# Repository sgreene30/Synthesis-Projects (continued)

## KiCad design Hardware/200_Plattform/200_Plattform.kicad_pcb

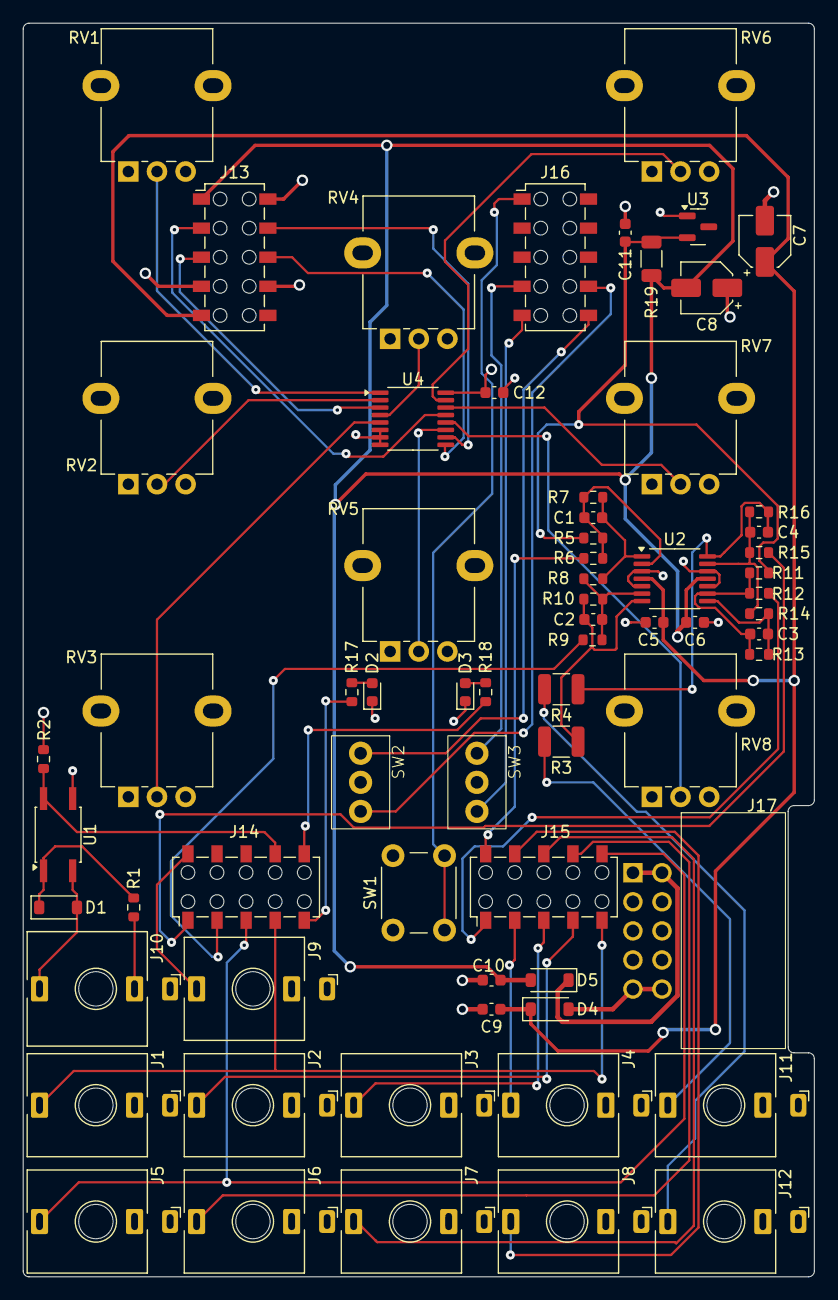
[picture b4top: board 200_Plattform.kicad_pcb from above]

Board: 4 copper layers, 69.1 x 109.5 mm, 69 parts (1 on the bottom side), 55 nets.

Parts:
C1, C2, C3, C4: 180pF; C_0603_1608Metric
C5, C6, C9, C10, C11, C12: 100nF; C_0603_1608Metric
C7, C8: 10uF; CAP_EEE-FK1V100UR
D1, D4, D5: MBR0530; D_SOD-123
D2, D3: LED_BLUE; LED_0603_1608Metric
J1, J2, J3, J4, J5, J6, J7, J8, J9, J11, J12: THONKICONN_MONO; JACK_THONKICONN_MONO_WQP518MA
J10: THONKICONN STEREO; JACK_THONKICONN_STEREO_WQP419GR
J13, J14, J15, J16: HEADER_2X10_BOTTOM_ENTRY_966210-2000-AR-PR
J17: EURO_POWER_10_RTANG
M1: DAISY PATCH SM; DAISY_PATCH_SM_OUTLINE
R1, R2, R17, R18: 220R; R_0603_1608Metric
R3, R4: 1k 0.5W; R_1210_3225Metric
R5, R7, R11, R13: 20k; R_0603_1608Metric
R6, R8, R9, R10, R12, R14, R15, R16: 10k; R_0603_1608Metric
R19: 6.8k 0.25W; R_1206_3216Metric
RV1, RV2, RV3, RV4, RV5, RV6, RV7, RV8: 10k; ALPHAPOT
SW1: SW_TACTILE; SW_TACTILE_TL1105SPF250Q
SW2, SW3: SW_SPDT_ON_OFF_ON_SUBMINI; SW_TOGGLE_2MS3T1B3M2QES
U1: LTV-355T; SO-4_4.4x3.6mm_P2.54mm
U2: TL074CPWR; TSSOP-14_4.4x5mm_P0.65mm
U3: LM4040CIM3-5.0; SOT-23
U4: CD4052B; TSSOP-16_4.4x5mm_P0.65mm

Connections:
+3.3V: C12.1, J13.10 (X10), R2.2, RV1.3, RV2.3, RV3.3, RV4.3, RV5.3, RV6.3, RV7.3, RV8.3, U4.16 (VDD)
+12V: C5.1, C7.1, C9.1, D4.1 (K), J13.5 (X5), U2.4 (V+)
-5V: C11.1, R5.1, R11.1, R19.1, U3.2 (A)
-12V: C6.2, C8.2, C10.2, D5.2 (A), J13.1 (X1), R19.2, U2.11 (V-)
/Jacks/MIDI_SINK: D1.2 (A), J10.T, U1.2
/Jacks/MIDI_SOURCE: J10.R, R1.1
AUDIO_LEFT: J14.2 (X2), R9.1
AUDIO_RIGHT: J14.1 (X1), R15.1
CV_OUT_1: J15.10 (X10), R6.2
CV_OUT_2: J15.1 (X1), R12.2
GATE_IN: J9.T, J14.10 (X10)
GND: C5.2, C6.1, C7.2, C8.1, C9.2, C10.1, C11.2, C12.2, D2.1 (K), D3.1 (K), J1.S, J2.S, J3.S, J4.S, J5.S, J6.S, J7.S, J8.S, J9.S, J11.S, J12.S, J13.4 (X4), J13.7 (X7), J17.3 (gnd), J17.4 (gnd), J17.5 (gnd), J17.6 (gnd), J17.7 (gnd), J17.8 (gnd), RV1.1, RV2.1, RV3.1, RV4.1, RV5.1, RV6.1, RV7.1, RV8.1, SW1.1, SW1.2, SW2.2 (B), SW3.2 (B), U1.3, U2.3 (+), U2.5 (+), U2.10 (+), U2.12 (+), U3.1 (K), U4.6 (INH), U4.7 (VEE), U4.8 (VSS)
LED_LEFT: J14.5 (X5), R17.2
LED_RIGHT: J14.6 (X6), R18.2
MIDI_UART_RX: J14.7 (X7), R2.1, U1.4
unnamed: C1.2, R7.2, R8.1, U2.1
unnamed: C3.2, R13.2, R14.1, U2.8
unnamed: D1.1 (K), R1.2, U1.1
unnamed: D2.2 (A), R17.1
unnamed: D3.2 (A), R18.1
unnamed: D4.2 (A), J17.9 (+12V), J17.10 (+12V)
unnamed: D5.1 (K), J17.1 (-12V), J17.2 (-12V)
unnamed: J11.T, R3.2
unnamed: J12.T, R4.2
unnamed: C1.1, R5.2, R6.1, R7.1, U2.2 (-)
unnamed: C2.1, R8.2, R9.2, R10.1, U2.6 (-)
unnamed: C3.1, R11.2, R12.1, R13.1, U2.9 (-)
unnamed: C4.1, R14.2, R15.2, R16.1, U2.13 (-)
POT_MUX_A: J13.9 (X9), U4.10 (A)
POT_MUX_ADC_X: J13.2 (X2), U4.13 (X)
POT_MUX_ADC_Y: J13.3 (X3), U4.3 (Y)
POT_MUX_B: J13.8 (X8), U4.9 (B)
TACTILE_SW: J16.1 (X1), SW1.3 (K), SW1.4 (A)
TOGGLE1_1: J16.6 (X6), SW2.1 (A)
TOGGLE1_3: J16.7 (X7), SW2.3 (C)
TOGGLE2_1: J16.4 (X4), SW3.1 (A)
TOGGLE2_3: J16.5 (X5), SW3.3 (C)
analog_out_1: C2.2, R3.1, R10.2, U2.7
analog_out_2: C4.2, R4.1, R16.2, U2.14
in_1: J1.T, J14.4 (X4), J15.5 (X5)
in_2: J2.T, J15.4 (X4)
in_3: J3.T, J15.3 (X3)
in_4: J4.T, J15.2 (X2)
in_5: J5.T, J14.3 (X3), J15.6 (X6)
in_6: J6.T, J15.7 (X7)
in_7: J7.T, J15.8 (X8)
in_8: J8.T, J15.9 (X9)
pot_1: RV1.2, U4.1 (Y0)
pot_2: RV2.2, U4.2 (Y2)
pot_3: RV3.2, U4.5 (Y1)
pot_4: RV4.2, U4.4 (Y3)
pot_5: RV5.2, U4.11 (X3)
pot_6: RV6.2, U4.15 (X2)
pot_7: RV7.2, U4.14 (X1)
pot_8: RV8.2, U4.12 (X0)

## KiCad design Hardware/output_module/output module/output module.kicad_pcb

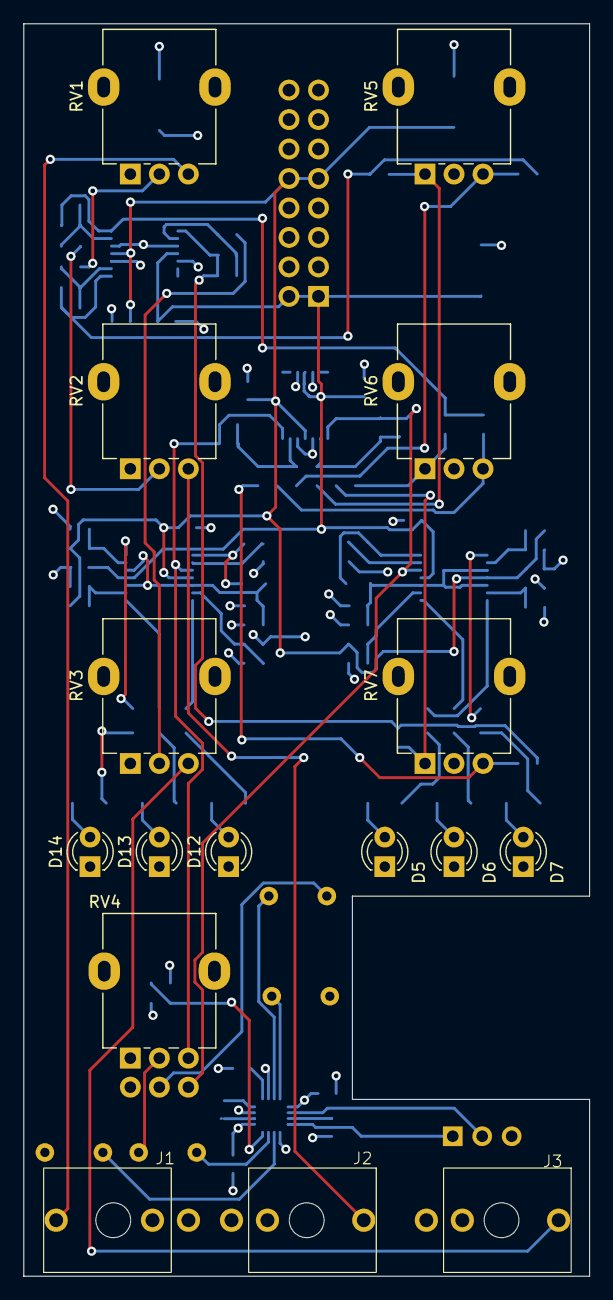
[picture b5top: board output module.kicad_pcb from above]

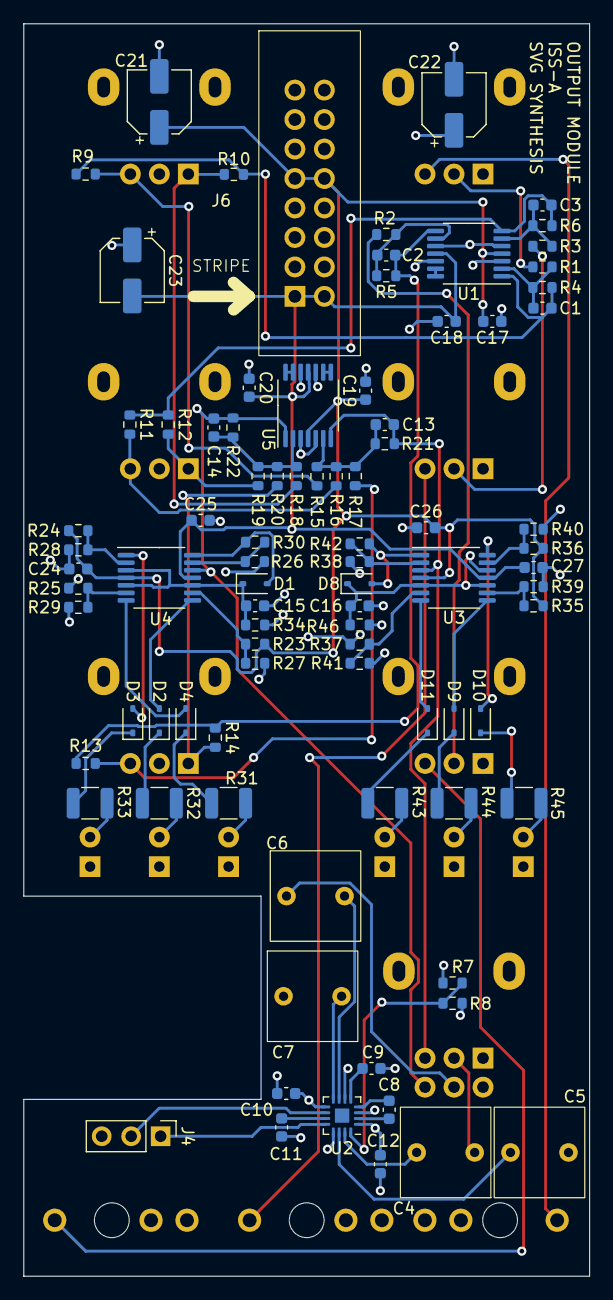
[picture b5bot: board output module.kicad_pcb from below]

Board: 4 copper layers, 48.8 x 108.0 mm, 104 parts (88 on the bottom side), 72 nets.

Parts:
C1, C2, C3, C13, C14: 47pF; C_0603_1608Metric
C4, C5, C6, C7: 2.2uF; C_Rect_L7.8mm_W7.8mm_P5.00mm
C8, C9, C10, C12: 1uF; C_0603_1608Metric
C11, C15, C16, C17, C18, C19, C20, C24, C25, C26, C27: 100nF; C_0603_1608Metric
C21, C22, C23: 10uF; CP_Elec_5x5.3
D1, D2, D3, D4, D8, D9, D10, D11: 1N4148; D_SOD-323
D5, D12: GREEN; LED_D3.0mm
D6, D13: YELLOW; LED_D3.0mm
D7, D14: RED; LED_D3.0mm
J1, J2, J3: thonkiconn
J4: Conn_01x03; PinHeader_1x03_P2.54mm_Vertical
J6: euro_power_16; eurorack_16
R1, R2, R3, R15, R16, R17, R18, R19, R20, R21, R22, R23, R24, R25, R26, R30, R34, R35, R36, R37, R38, R42, R46: 100k; R_0603_1608Metric
R4, R5, R6: 68k; R_0603_1608Metric
R7, R8, R9, R10, R11, R12, R13, R14: 10k; R_0603_1608Metric
R27, R39: 22k; R_0603_1608Metric
R28, R40: 27k; R_0603_1608Metric
R29, R41: 1k; R_0603_1608Metric
R31, R32, R33, R43, R44, R45: 1k 0.5W; R_1210_3225Metric
RV1, RV2, RV3: A100k; Potentiometer_Alpha_RD901F-40-00D_Single_Vertical
RV4: A10K; Potentiometer_Alpha_RD902F-40-00D_Dual_Vertical
RV5, RV6, RV7: 10k; Potentiometer_Alpha_RD901F-40-00D_Single_Vertical
U1, U3, U4, U5: TL074; TSSOP-14_4.4x5mm_P0.65mm
U2: MAX97220C; TQFN-16-1EP_3x3mm_P0.5mm_EP1.23x1.23mm

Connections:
+5V: C10.1, C12.1, C22.1, J6.11 (+5V), J6.12 (+5V), R7.1, R25.2, R37.2, U2.1 (PVDD), U2.9 (SVDD2), U2.13 (SVDD)
+12V: C17.1, C19.1, C21.1, C24.1, C26.1, J6.9 (+12V), J6.10 (+12V), R23.2, R24.2, R35.2, R36.2, U1.4 (V+), U3.4 (V+), U4.4 (V+), U5.4 (V+)
-12V: C18.2, C20.2, C23.2, C25.2, C27.2, J6.1 (-12V), J6.2 (-12V), U1.11 (V-), U3.11 (V-), U4.11 (V-), U5.11 (V-)
GND: C5.1, C7.1, C9.2, C10.2, C11.2, C12.2, C15.2, C16.2, C17.2, C18.1, C19.2, C20.1, C21.2, C22.2, C23.1, C24.2, C25.1, C26.2, C27.1, D5.1 (K), D6.1 (K), D7.1 (K), D12.1 (K), D13.1 (K), D14.1 (K), J1.S, J2.S, J3.S, J4.3, J6.3 (gnd), J6.4 (gnd), J6.5 (gnd), J6.6 (gnd), J6.7 (gnd), J6.8 (gnd), R8.2, R26.1, R27.2, R28.2, R29.2, R34.1, R38.1, R39.2, R40.2, R41.2, R46.1, RV1.1, RV2.1, RV3.1, RV4.1, RV4.4, RV5.2, RV6.2, RV7.2, U1.3 (+), U1.5 (+), U1.10 (+), U1.12 (+), U2.3 (PGND), U2.6 (SGND), U5.3 (+), U5.5 (+), U5.10 (+), U5.12 (+)
unnamed: C4.1, RV4.2
unnamed: C6.1, RV4.5
unnamed: D1.2 (A), R30.2, U4.14
unnamed: D2.2 (A), U4.8
unnamed: D2.1 (K), R32.1
unnamed: D3.2 (A), U4.1
unnamed: D3.1 (K), R33.1
unnamed: D4.2 (A), U4.7
unnamed: D4.1 (K), R31.1
unnamed: D5.2 (A), R31.2
unnamed: D6.2 (A), R32.2
unnamed: D7.2 (A), R33.2
unnamed: D8.2 (A), R42.2, U3.1
unnamed: D9.2 (A), U3.8
unnamed: D9.1 (K), R44.1
unnamed: D10.2 (A), U3.14
unnamed: D10.1 (K), R45.1
unnamed: D11.2 (A), U3.7
unnamed: D11.1 (K), R43.1
unnamed: D12.2 (A), R43.2
unnamed: D13.2 (A), R44.2
unnamed: D14.2 (A), R45.2
unnamed: J1.T, RV1.3
unnamed: J2.T, RV2.3
unnamed: J3.T, RV3.3
unnamed: R1.1, RV1.2
unnamed: R2.1, RV3.2
unnamed: R3.1, RV2.2
unnamed: C1.1, R1.2, R4.1, U1.2 (-)
unnamed: C3.1, R3.2, R6.1, U1.6 (-)
unnamed: C2.1, R2.2, R5.1, U1.9 (-)
unnamed: U1.13 (-), U1.14
unnamed: C11.1, U2.11 (BIAS)
unnamed: C8.1, U2.4 (C1N)
unnamed: C8.2, U2.2 (C1P)
unnamed: C4.2, U2.15 (INL+)
unnamed: C5.2, U2.14 (INL-)
unnamed: C6.2, U2.7 (INR+)
unnamed: C7.2, U2.8 (INR-)
unnamed: C9.1, U2.5 (PVSS)
unnamed: R38.2, R42.1, U3.2 (-)
unnamed: R37.1, R41.1, U3.6 (-)
unnamed: R35.1, R39.1, U3.9 (-)
unnamed: R36.1, R40.1, U3.13 (-)
unnamed: R24.1, R28.1, U4.2 (-)
unnamed: R25.1, R29.1, U4.6 (-)
unnamed: R23.1, R27.1, U4.9 (-)
unnamed: R26.2, R30.1, U4.13 (-)
unnamed: C14.1, R18.2, R19.2, R20.2, R22.1, U5.2 (-)
unnamed: C13.1, R15.2, R16.2, R17.2, R21.1, U5.6 (-)
unnamed: U5.8, U5.9 (-)
unnamed: U5.13 (-), U5.14
SHDN: R7.2, R8.1, U2.16 (SHDN)
chan_1: C1.2, R4.2, R9.1, R10.1, U1.1
chan_1_left: R9.2, R15.1, RV5.3
chan_1_right: R10.2, R18.1, RV5.1
chan_2: C3.2, R6.2, R11.1, R12.1, U1.7
chan_2_left: R11.2, R16.1, RV6.3
chan_2_right: R12.2, R19.1, RV6.1
chan_3: C2.2, R5.2, R13.1, R14.1, U1.8
chan_3_left: R13.2, R17.1, RV7.3
chan_3_right: R14.2, R20.1, RV7.1
left_mix: C13.2, R21.2, RV4.3, U3.3 (+), U5.7
left_out: J4.1, U2.12 (OUTL)
left_peak: C16.1, D8.1 (K), R46.2, U3.5 (+), U3.10 (+), U3.12 (+)
right_mix: C14.2, R22.2, RV4.6, U4.12 (+), U5.1
right_out: J4.2, U2.10 (OUTR)
right_peak: C15.1, D1.1 (K), R34.2, U4.3 (+), U4.5 (+), U4.10 (+)

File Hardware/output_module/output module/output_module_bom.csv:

"Reference","Value","Datasheet","Footprint","Qty","DNP","MFR","MPN","Description"
"C1,C2,C3,C13,C14","47pF","~","Capacitor_SMD:C_0603_1608Metric","5","","YAGEO","CC0603JRNPO9BN470",""
"C4,C5,C6,C7","2.2uF","~","Capacitor_THT:C_Rect_L7.2mm_W4.5mm_P5.00mm_FKS2_FKP2_MKS2_MKP2","4","DNP","EPCOS TDK","B32529D0225K000","CAP FILM 2.2UF 10% 63VDC RADIAL"
"C8,C9,C10,C12","1uF","~","Capacitor_SMD:C_0603_1608Metric","4","","YAGEO","CC0603KRX7R8BB105",""
"C11,C15,C16,C17,C18,C19,C20,C24,C25,C26,C27","100nF","~","Capacitor_SMD:C_0603_1608Metric","11","","YAGEO","CC0603KRX7R9BB104",""
"C21,C22,C23","10uF","~","Capacitor_SMD:CP_Elec_5x5.3","3","","WURTH","865250442003",""
"D1,D2,D3,D4,D8,D9,D10,D11","1N4148","","Diode_SMD:D_SOD-323","8","","DIODES INC","1N4148WS-7-F",""
"D5,D12","GREEN","~","LED_THT:LED_D3.0mm","2","DNP","WURTH","151031VS04000",""
"D6,D13","YELLOW","~","LED_THT:LED_D3.0mm","2","DNP","WURTH","151031YS06000",""
"D7,D14","RED","~","LED_THT:LED_D3.0mm","2","DNP","WURTH","151031SS04000",""
"J1,J2,J3","thonkiconn","~","synthesis:thonkiconn","3","DNP","QINGPU","WQP518MA",""
"J4","Conn_01x03","~","Connector_PinHeader_2.54mm:PinHeader_1x03_P2.54mm_Vertical","1","DNP","","",""
"J6","euro_power_16","","synthesis:eurorack_16","1","DNP","CNC Tech","3020-16-0100-00",""
"R1,R2,R3,R15,R16,R17,R18,R19,R20,R21,R22,R23,R24,R25,R26,R30,R34,R35,R36,R37,R38,R42,R46","100k","","Resistor_SMD:R_0603_1608Metric","23","","RC0603FR-07100KL","RC0603FR-07100KL",""
"R4,R5,R6","68k","","Resistor_SMD:R_0603_1608Metric","3","","YAGEO","RC0603FR-0768KL",""
"R7,R8,RV5,RV6,RV7","10k","-- mixed values --","-- mixed values --","5","DNP","-- mixed values --","-- mixed values --",""
"R9,R10,R11,R12,R13,R14","10k","","Resistor_SMD:R_0603_1608Metric","6","","YAGEO","RC0603FR-0710KL",""
"R27,R39","22k","","Resistor_SMD:R_0603_1608Metric","2","","YAGEO","RC0603FR-0722KL",""
"R28,R40","27k","","Resistor_SMD:R_0603_1608Metric","2","","YAGEO","RC0603FR-0727KL",""
"R29,R41","1k","","Resistor_SMD:R_0603_1608Metric","2","","YAGEO","RC0603FR-071KL",""
"R31,R32,R33,R43,R44,R45","1k 0.5W","","Resistor_SMD:R_1210_3225Metric","6","","YAGEO","RC1210FR-071KL",""
"RV1,RV2,RV3","A100k","~","Potentiometer_THT:Potentiometer_Alpha_RD901F-40-00D_Single_Vertical","3","DNP","ALPHA","A100K",""
"RV4","A10K","~","Potentiometer_THT:Potentiometer_Alpha_RD902F-40-00D_Dual_Vertical","1","DNP","ALPHA","A10K DUAL",""
"U1,U3,U4,U5","TL074","http://www.ti.com/lit/ds/symlink/lm2902-n.pdf","Package_SO:TSSOP-14_4.4x5mm_P0.65mm","4","","TI","TL074CPWR",""
"U2","MAX97220C","","Package_DFN_QFN:TQFN-16-1EP_3x3mm_P0.5mm_EP1.23x1.23mm","1","DNP","Analog Devices","MAX97220CETE+T",""

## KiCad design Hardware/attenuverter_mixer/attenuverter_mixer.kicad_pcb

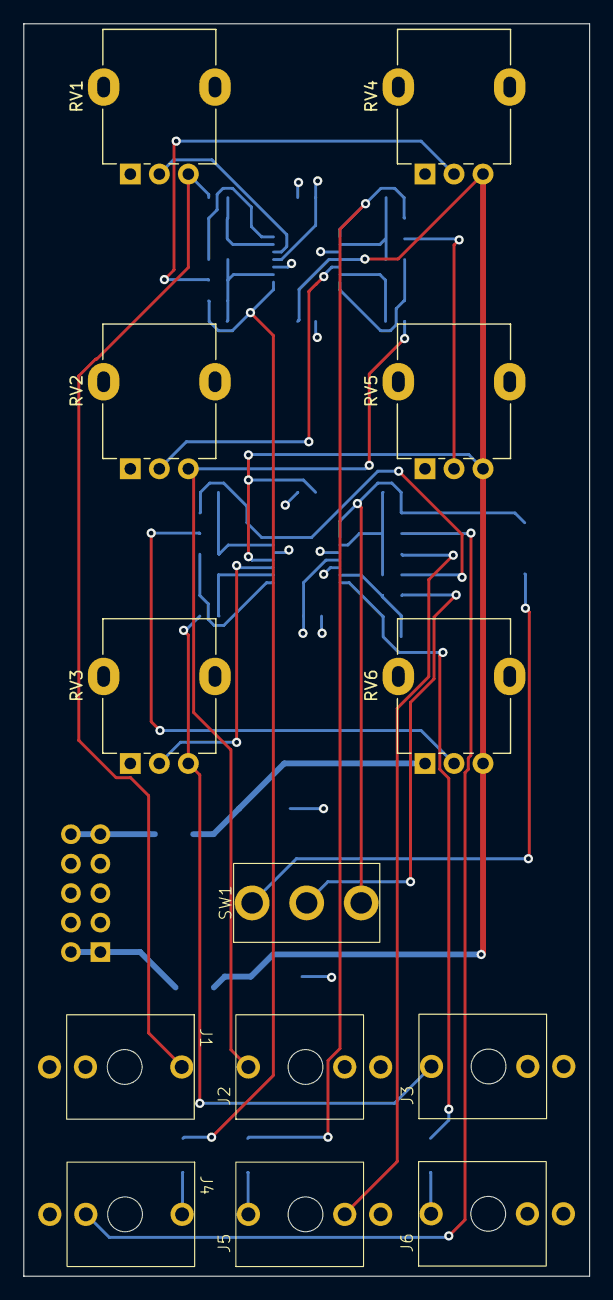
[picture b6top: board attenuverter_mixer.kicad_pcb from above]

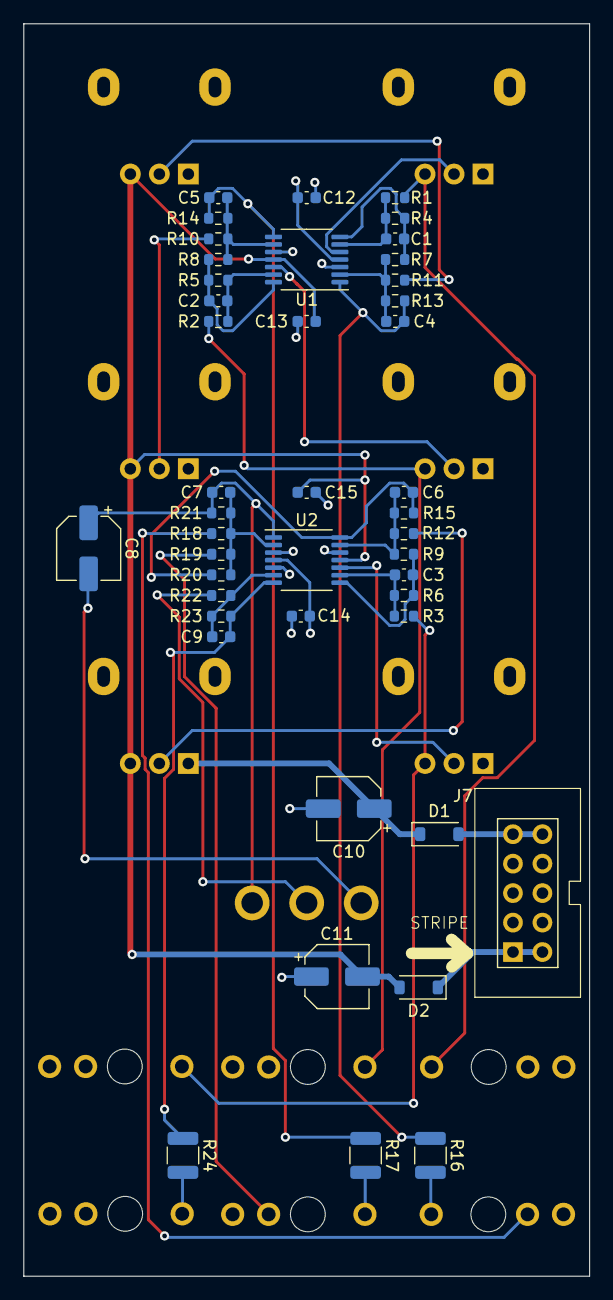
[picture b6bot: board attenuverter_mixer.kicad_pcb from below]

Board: 4 copper layers, 48.8 x 107.9 mm, 57 parts (44 on the bottom side), 37 nets.

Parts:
C1, C2, C3, C4, C5, C6, C7, C9: 47pF; C_0603_1608Metric
C8, C10, C11: 10uF; CP_Elec_5x5.3
C12, C13, C14, C15: 100nF; C_0603_1608Metric
D1, D2: MBR0530; D_SOD-123
J1, J2, J3, J4, J5, J6: thonkiconn
J7: euro_power_10; eurorack_10
R1, R2, R3, R4, R5, R6, R18, R19, R20, R23: 100k; R_0603_1608Metric
R7, R8, R9, R13, R14, R15: 10k; R_0603_1608Metric
R10, R11, R12, R21, R22: 24k; R_0603_1608Metric
R16, R17, R24: 1k 0.5W; R_1210_3225Metric
RV1, RV2, RV3, RV4, RV5, RV6: 10k; Potentiometer_Alpha_RD901F-40-00D_Single_Vertical
SW1: SW_ON_ON_SPDT_MINI; Mini_sw
U1, U2: TL074; TSSOP-14_4.4x5mm_P0.65mm

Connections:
+12V: C10.1, C12.1, C14.1, D1.1 (K), RV4.1, RV5.1, RV6.1, U1.4 (V+), U2.4 (V+)
-12V: C11.2, C13.2, C15.2, D2.2 (A), RV4.3, RV5.3, RV6.3, U1.11 (V-), U2.11 (V-)
/Power/V+_IN: D1.2 (A), J7.9 (+12V), J7.10 (+12V)
/Power/V-_IN: D2.1 (K), J7.1 (-12V), J7.2 (-12V)
GND: C10.2, C11.1, C12.2, C13.1, C14.2, C15.1, J1.S, J2.S, J3.S, J4.S, J5.S, J6.S, J7.3 (gnd), J7.4 (gnd), J7.5 (gnd), J7.6 (gnd), J7.7 (gnd), J7.8 (gnd), RV1.1, RV2.1, RV3.1, U1.3 (+), U1.10 (+), U2.3 (+), U2.5 (+), U2.12 (+)
unnamed: C1.2, R4.2, R7.1, U1.7
unnamed: C2.2, R5.2, R8.1, U1.14
unnamed: C3.2, R6.2, R9.1, U2.8
unnamed: C4.2, R13.2, R16.1, U1.1
unnamed: C5.2, R14.2, R17.1, U1.8
unnamed: C9.2, R23.2, R24.1, U2.7
unnamed: J1.T, R1.1, RV1.3
unnamed: J2.T, R2.1, RV2.3
unnamed: J3.T, R3.1, RV3.3
unnamed: J4.T, R16.2
unnamed: J5.T, R17.2
unnamed: J6.T, R24.2
unnamed: C7.2, C8.1, R21.2, SW1.1 (A), U2.1
unnamed: R22.1, SW1.2 (B)
unnamed: C8.2, SW1.3 (C)
unnamed: C4.1, R7.2, R11.2, R13.1, U1.2 (-)
unnamed: RV1.2, U1.5 (+)
unnamed: C1.1, R1.2, R4.1, U1.6 (-)
unnamed: C5.1, R8.2, R10.2, R14.1, U1.9 (-)
unnamed: RV2.2, U1.12 (+)
unnamed: C2.1, R2.2, R5.1, U1.13 (-)
unnamed: C7.1, R18.2, R19.2, R20.2, R21.1, U2.2 (-)
unnamed: C9.1, R22.2, R23.1, U2.6 (-)
unnamed: RV3.2, U2.10 (+)
unnamed: C3.1, R3.2, R6.1, U2.9 (-)
unnamed: C6.1, R9.2, R12.2, R15.1, U2.13 (-)
att_1_out: J4.TN, R18.1
att_2_out: J5.TN, R19.1
att_3_out: C6.2, R15.2, R20.1, U2.14
offset_1: R11.1, RV4.2
offset_2: R10.1, RV5.2
offset_3: R12.1, RV6.2

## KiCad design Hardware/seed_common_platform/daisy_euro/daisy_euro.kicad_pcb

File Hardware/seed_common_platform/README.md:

# Daisy Seed Common Platform

This hardware project implements a eurorack compliant breakout board for the daisy seed

## Features
- 8 potentiometer controls 
- momentary PB
- 3 POS Switch x 2
- multiplexed 
- configurable jacks

### Configurable Jack IO: 
- stereo audio IO
- DAC outputs x 2
- CV inputs x 8
- gate output x 2

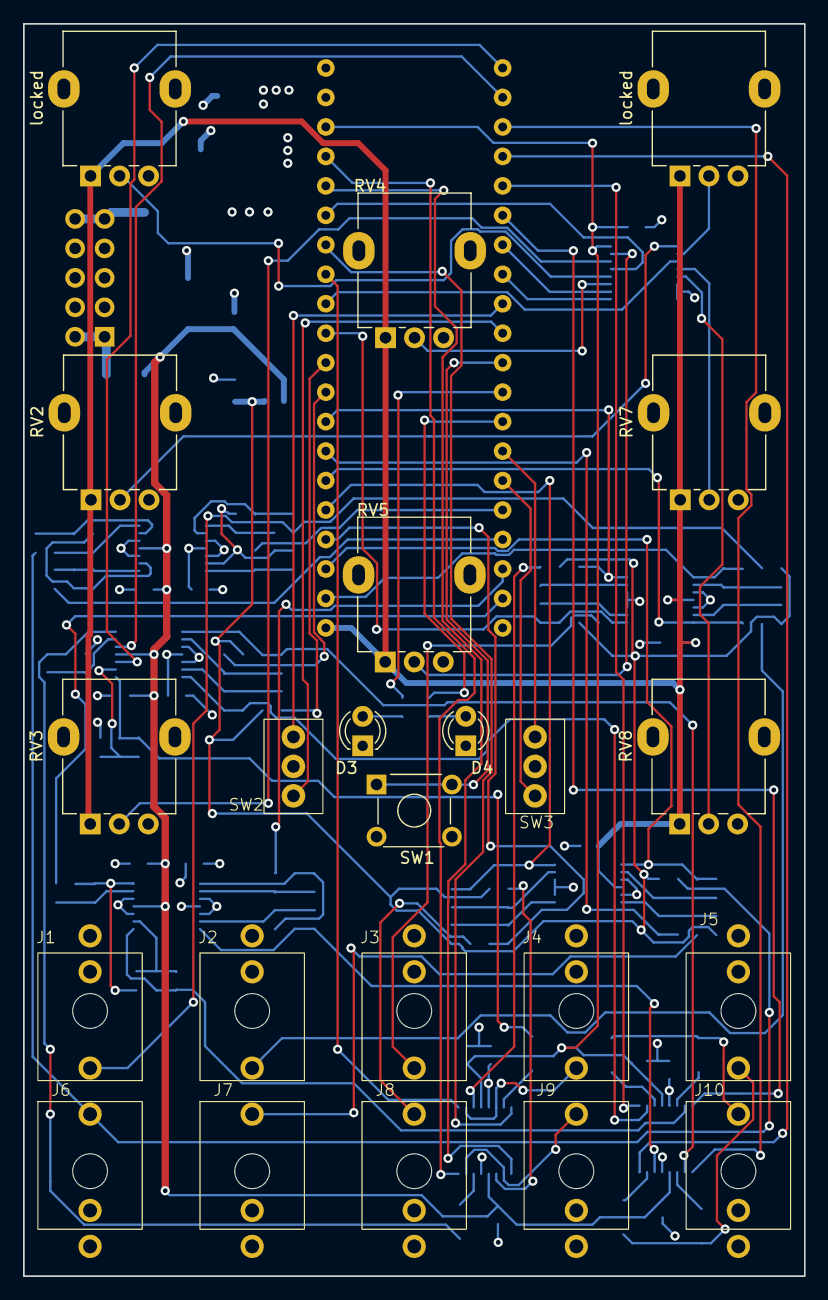
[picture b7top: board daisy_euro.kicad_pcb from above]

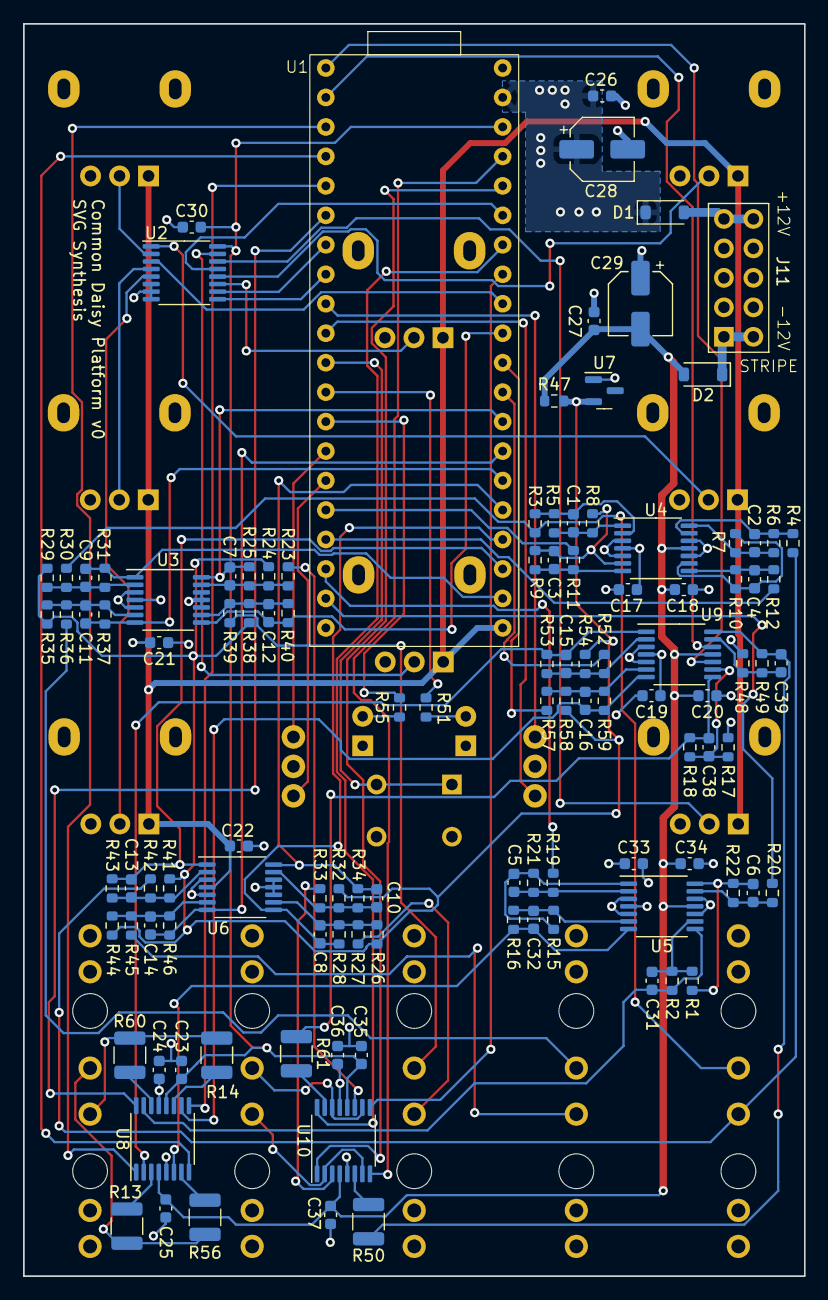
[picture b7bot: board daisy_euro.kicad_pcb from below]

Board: 4 copper layers, 67.3 x 107.9 mm, 136 parts (113 on the bottom side), 103 nets.

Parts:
C1, C2: 20p; C_0603_1608Metric
C3, C4, C5, C6, C31, C32, C38, C39: 180p; C_0603_1608Metric
C7, C8, C9, C10, C11, C12, C13, C14, C15, C16: 1n; C_0603_1608Metric
C17, C18, C19, C20, C21, C22, C23, C24, C25, C26, C27, C30, C33, C34, C35, C36, C37: 100n; C_0603_1608Metric
C28, C29: 10uF; CP_Elec_5x5.4
D1, D2: MBR0530-TP; D_SOD-123
D3, D4: LED; LED_D3.0mm
J1, J2, J3, J4, J5, J6, J7, J8, J9, J10: thonkiconn
J11: euro_power_10; eurorack_10
R1, R2, R15, R16, R19, R20: 10k; R_0603_1608Metric
R3, R4, R18, R23, R27, R30, R33, R36, R39, R42, R45, R49, R53, R59: 100k; R_0603_1608Metric
R5, R6: 220k; R_0603_1608Metric
R7, R8: 270k; R_0603_1608Metric
R9, R10, R25, R28, R31, R34, R37, R40, R43, R46, R52, R57: 33k; R_0603_1608Metric
R11, R12: 1k; R_0603_1608Metric
R13, R14, R50, R56, R60, R61: 1k; C_1210_3225Metric
R17, R24, R26, R29, R32, R35, R38, R41, R44, R48, R54, R58: 200k; R_0603_1608Metric
R21, R22: 30k; R_0603_1608Metric
R47: 2k; R_0603_1608Metric
R51, R55: 200R; R_0603_1608Metric
RV2, RV3, RV4, RV5, RV7, RV8: 10k; Potentiometer_Alpha_RD901F-40-00D_Single_Vertical
SW1: SW_Push; SW_TH_Tactile_Omron_B3F-10xx
SW2, SW3: SW_SPDT_MSM; subminiature_toggle_spdt_mom
U1: daisy_seed
U2: CD4052BPWR; TSSOP-16_4.4x5mm_P0.65mm
U3, U6: MCP6004; TSSOP-14_4.4x5mm_P0.65mm
U4, U5, U9: TL074CPWR; TSSOP-14_4.4x5mm_P0.65mm
U7: LM4040DBZ-10; SOT-23
U8, U10: DG412DQ-T1-E3; TSSOP-16_4.4x5mm_P0.65mm
locked: 10k; Potentiometer_Alpha_RD901F-40-00D_Single_Vertical
locked#2: 10k; Potentiometer_Alpha_RD901F-40-00D_Single_Vertical

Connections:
+3.3V: C23.1, C30.1, C35.1, U1.38 (3V3_Digital), U2.16 (VDD), U8.12 (VL), U10.12 (VL)
+3.3VA: C21.1, C22.1, RV2.1, RV3.1, RV4.1, RV5.1, RV7.1, RV8.1, U1.21 (3V3_Analog), U3.4 (V+), U6.4 (V+), locked.1, locked#2.1
+12V: C17.1, C19.1, C24.1, C26.1, C28.1, C33.1, C36.1, D1.1 (K), U1.39 (VIN), U4.4 (V+), U5.4 (V+), U8.13 (V+), U9.4 (V+), U10.13 (V+)
-10V: R24.1, R26.1, R29.1, R32.1, R35.1, R38.1, R41.1, R44.1, R47.2, R54.1, R58.1, U7.2 (A)
-12V: C18.2, C20.2, C25.2, C27.2, C29.2, C34.2, C37.2, D2.2 (A), R47.1, U4.11 (V-), U5.11 (V-), U8.4 (V-), U9.11 (V-), U10.4 (V-)
/cv/pot_1: U2.12 (X0), locked#2.2
/cv/pot_2: RV3.2, U2.14 (X1)
/cv/pot_3: RV5.2, U2.15 (X2)
/cv/pot_4: RV7.2, U2.4 (Y3)
/cv/pot_5: RV2.2, U2.1 (Y0)
/cv/pot_6: RV4.2, U2.11 (X3)
/cv/pot_7: U2.2 (Y2), locked.2
/cv/pot_8: RV8.2, U2.5 (Y1)
A0_D15: C9.1, R31.2, U1.22 (A0/D15), U3.1
A1_D16: C13.1, R43.2, U1.23 (A1/D16), U6.1
A2_D17: C8.1, R28.2, U1.24 (A2/D17), U6.8
A3_D18: C10.1, R34.2, U1.25 (A3/D18), U6.14
A4_D19: C11.1, R37.2, U1.26 (A4/D19), U3.7
A5_D20: C14.1, R46.2, U1.27 (A5/D20), U6.7
A6_D21: C7.1, R25.2, U1.28 (A6/D21), U3.14
A7_D22: R52.1, U1.29 (A7/D22)
A8_D23: R57.1, U1.30 (A8/D23)
A9_D24: C12.1, R40.2, U1.31 (A9/D24), U3.8
A10_D25: U1.32 (A10/D25), U2.3 (Y)
A11_D28: U1.35 (A11/D28), U2.13 (X)
D0: U1.1 (D0), U9.10 (+)
D1: U1.2 (D1), U9.12 (+)
D2: U1.3 (D2), U8.1
D3: U1.4 (D3), U8.8
D4: U1.5 (D4), U8.9
D5: U1.6 (D5), U8.16
D6: U1.7 (D6), U2.10 (A)
D7: U1.8 (D7), U2.9 (B)
D8: SW2.1, U1.9 (D8)
D9: SW2.3, U1.10 (D9)
D10: SW1.1, U1.11 (D10)
D11: R51.2, U1.12 (D11)
D12: R55.2, U1.13 (D12)
D13: SW3.1, U1.14 (D13)
D14: SW3.3, U1.15 (D14)
D26: U1.33 (D26), U10.9
D27: U1.34 (D27), U10.16
D29: U1.36 (D29), U10.1
D30: U1.37 (D30), U10.8
GND: C17.2, C18.1, C19.2, C20.1, C21.2, C22.2, C23.2, C24.2, C25.1, C26.2, C27.1, C28.2, C29.1, C30.2, C33.2, C34.1, C35.2, C36.2, C37.1, D3.1 (K), D4.1 (K), J1.S, J2.S, J3.S, J4.S, J5.S, J6.S, J7.S, J8.S, J9.S, J10.S, J11.3 (gnd), J11.4 (gnd), J11.5 (gnd), J11.6 (gnd), J11.7 (gnd), J11.8 (gnd), R17.1, R48.1, RV2.3, RV3.3, RV4.3, RV5.3, RV7.3, RV8.3, SW1.2, SW2.2, SW3.2, U1.20 (AGND), U1.40 (DGND), U2.6 (INH), U2.7 (VEE), U2.8 (VSS), U3.3 (+), U3.5 (+), U3.10 (+), U3.11 (V-), U3.12 (+), U4.3 (+), U4.5 (+), U4.10 (+), U4.12 (+), U5.3 (+), U5.5 (+), U5.10 (+), U5.12 (+), U6.3 (+), U6.5 (+), U6.10 (+), U6.11 (V-), U6.12 (+), U7.1 (K), U8.5 (GND), U9.3 (+), U9.5 (+), U10.5 (GND), locked.3, locked#2.3
J1_cv_a_in: J1.T, R3.1, R30.1
J6_cv_a_in: J6.T, R4.1, R42.1
unnamed: C1.1, R5.2, R8.1, U4.1
unnamed: C2.1, R6.2, R7.1, U4.14
unnamed: C3.1, R9.2, R11.1, U4.7
unnamed: C4.1, R10.2, R12.1, U4.8
unnamed: C5.1, R15.1, R21.2, U5.1
unnamed: C6.1, R1.1, R22.2, U5.14
unnamed: C38.1, R18.2, R61.1, U9.8
unnamed: C39.1, R49.2, R50.1, U9.14
unnamed: D1.2 (A), J11.9 (+12V), J11.10 (+12V)
unnamed: D2.1 (K), J11.1 (-12V), J11.2 (-12V)
unnamed: D3.2 (A), R51.1
unnamed: D4.2 (A), R55.1
unnamed: J4.T, U10.10, U10.14
unnamed: J5.T, R13.2, R56.2
unnamed: J9.T, U10.2, U10.7
unnamed: J10.T, R14.2, R60.2
unnamed: R13.1, U8.3
unnamed: R14.1, U8.11
unnamed: R56.1, U8.7
unnamed: R60.1, U8.14
unnamed: C9.2, R29.2, R30.2, R31.1, U3.2 (-)
unnamed: C11.2, R35.2, R36.2, R37.1, U3.6 (-)
unnamed: C12.2, R38.2, R39.2, R40.1, U3.9 (-)
unnamed: C7.2, R23.2, R24.2, R25.1, U3.13 (-)
unnamed: C1.2, R3.2, R5.1, U4.2 (-)
unnamed: C3.2, R8.2, R9.1, U4.6 (-)
unnamed: C4.2, R7.2, R10.1, U4.9 (-)
unnamed: C2.2, R4.2, R6.1, U4.13 (-)
unnamed: C5.2, R19.2, R21.1, U5.2 (-)
unnamed: C32.2, R15.2, R16.1, U5.6 (-)
unnamed: C31.2, R1.2, R2.1, U5.9 (-)
unnamed: C6.2, R20.2, R22.1, U5.13 (-)
unnamed: C13.2, R41.2, R42.2, R43.1, U6.2 (-)
unnamed: C14.2, R44.2, R45.2, R46.1, U6.6 (-)
unnamed: C8.2, R26.2, R27.2, R28.1, U6.9 (-)
unnamed: C10.2, R32.2, R33.2, R34.1, U6.13 (-)
unnamed: C15.2, R52.2, R53.1, R54.2, U9.2 (-)
unnamed: C16.2, R57.2, R58.2, R59.1, U9.6 (-)
unnamed: C38.2, R17.2, R18.1, U9.9 (-)
unnamed: C39.2, R48.2, R49.1, U9.13 (-)
audio_out_0: C32.1, R16.2, U5.7, U8.6
audio_out_1: C31.1, R2.2, U5.8, U8.15
cv_in_2: J2.T, R36.1
cv_in_3: J7.T, R45.1
cv_in_4: J3.T, R39.1
cv_in_5: J8.T, R27.1
cv_in_6: R23.1, U10.11
cv_in_7: R33.1, U10.3
cv_out_0: C15.1, R53.2, U8.2, U9.1
cv_out_1: C16.1, R59.2, U8.10, U9.7
gate_out_0: R61.2, U10.15
gate_out_1: R50.2, U10.6
in_0: R11.2, U1.16 (in[0])
in_1: R12.2, U1.17 (in[1])
out_0: R19.1, U1.18 (out[0])
out_1: R20.1, U1.19 (out[1])

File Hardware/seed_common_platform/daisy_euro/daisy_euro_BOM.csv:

Source:,C:\Users\samue\Documents\synth_projects\seed_common_platform\daisy_euro\daisy_euro.kicad_sch,,,,,,,
Date:,12/30/2023 12:17,,,,,,,
Tool:,Eeschema 7.0.1,,,,,,,
Generator:,C:\Program Files\KiCad\7.0\bin\scripting\plugins/bom_csv_grouped_by_value.py,,,,,,,
Component Count:,136,,,,,,,
,,,,,,,,
Collated Components:,,,,,,,,
,,,,,,,,
Item,Qty,Comment,Footprint,DNP,LCSC Part Number,MFR PN,PCBA,Reference(s)
1,2,20pF,603,,C1648,CL10C200JB8NNNC,yes,"C1, C2"
2,8,180pF,603,,C107041,CC0603JRNPO9BN181,yes,"C3, C4, C5, C6, C31, C32, C38, C39"
3,10,1nF,603,,C1588,CL10B102KB8NNNC,yes,"C7, C8, C9, C10, C11, C12, C13, C14, C15, C16"
4,17,100nF,603,,C14663,CC0603KRX7R9BB104,yes,"C17, C18, C19, C20, C21, C22, C23, C24, C25, C26, C27, C30, C33, C34, C35, C36, C37"
5,2,10uF,,,,,yes,"C28, C29"
6,2,MBR0530-TP,SOD-123,,C8598,,yes,"D1, D2"
7,2,LED,,,,,no,"D3, D4"
8,10,thonkiconn,,,,,no,"J1, J2, J3, J4, J5, J6, J7, J8, J9, J10"
9,1,euro_power_10,,,,,no,J11
10,6,10k,603,,C25804,0603WAF1002T5E,yes,"R1, R2, R15, R16, R19, R20"
11,14,100k,603,,C25803,0603WAF1003T5E,yes,"R3, R4, R18, R23, R27, R30, R33, R36, R39, R42, R45, R49, R53, R59"
12,2,220k,603,,C22961,0603WAF2203T5E,yes,"R5, R6"
13,2,270k,603,,C307293,RK73B1JTTD274J,yes,"R7, R8"
14,12,33k,603,,C4216,0603WAF3302T5E,yes,"R9, R10, R25, R28, R31, R34, R37, R40, R43, R46, R52, R57"
15,2,1k,603,,C21190,0603WAF1001T5E,yes,"R11, R12"
16,6,1k,1210,,C516147,RK73H2ETTD1001F,yes,"R13, R14, R50, R56, R60, R61"
17,12,200k,603,,C25811,,yes,"R17, R24, R26, R29, R32, R35, R38, R41, R44, R48, R54, R58"
18,2,30k,603,,C22984,0603WAF3002T5E,yes,"R21, R22"
19,1,2k,603,,C22975,0603WAF2001T5E,yes,R47
20,2,200R,603,,C8218,0603WAF2000T5E,yes,"R51, R55"
21,8,10k,,,,,no,"RV1, RV2, RV3, RV4, RV5, RV6, RV7, RV8"
22,1,SW_Push,,,,,no,SW1
23,2,SW_SPDT_MSM,,,,,no,"SW2, SW3"
24,1,daisy_seed,,,,,no,U1
25,1,CD4052BPWR,TSSOP-16,,C6522,CD4052BPWR,yes,U2
26,2,MCP6004,TSSOP-14,,C50282,MCP6004,yes,"U3, U6"
27,3,TL074CPWR,TSSOP-14,,C96507,TL074CPWR,yes,"U4, U5, U9"
28,1,LM4040DBZ-10,,,,LM4040DBZ-10,no,U7
29,2,DG412DQ-T1-E3,TSSOP-16,,C2651920,DG412DQ-T1-E3,yes,"U8, U10"

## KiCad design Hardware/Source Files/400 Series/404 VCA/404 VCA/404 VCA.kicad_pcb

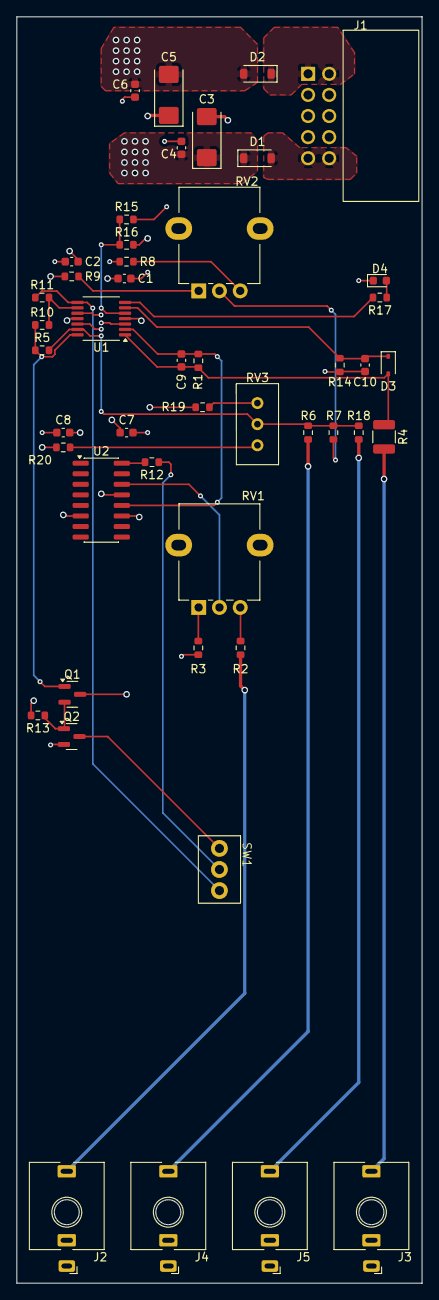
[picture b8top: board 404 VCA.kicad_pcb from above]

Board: 4 copper layers, 48.8 x 152.4 mm, 47 parts (0 on the bottom side), 31 nets.

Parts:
C1, C2, C4, C6, C7, C8, C10: 100nF; C_0603_1608Metric
C3, C5: 10uF; C_P_2312_6032
C9: 100pF; C_0603_1608Metric
D1, D2: MBR0530; D_SOD-123
D3: 1N4148; D_SOD-323
D4: LED_BLUE; LED_0603_1608Metric
J1: EURO_POWER_10_RTANG
J2, J3, J4, J5: THONKICONN_MONO; JACK_THONKICONN_MONO_WQP518MA
Q1: MMBT3904; SOT-23
Q2: MMBT3906; SOT-23
R1: 56k; R_0603_1608Metric
R2, R6, R7, R11, R13, R18: 100k; R_0603_1608Metric
R3: 100R; R_0603_1608Metric
R4: 1k 0.5W; R_1210_3225Metric
R5, R8, R9, R10, R17, R19, R20: 2.2k; R_0603_1608Metric
R12, R15: 22k; R_0603_1608Metric
R14: 220k; R_0603_1608Metric
R16: 33k; R_0603_1608Metric
RV1, RV2: 10k; ALPHAPOT
RV3: 5K; TRIMPOT_PV36
SW1: SW_SPDT_ON_OFF_ON_SUBMINI; SW_TOGGLE_2MS3T1B3M2QES
U1: TL074CPWR; TSSOP-14_4.4x5mm_P0.65mm
U2: LM13700; SOIC-16_3.9x9.9mm_P1.27mm

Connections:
+12V: C1.1, C3.1, C4.1, C7.1, D1.1 (K), Q1.3 (C), R8.2, R16.1, R19.2, U1.4 (V+), U2.11 (V+)
-12V: C2.2, C5.2, C6.2, C8.2, D2.2 (A), R9.1, R13.1, R20.1, U1.11 (V-), U2.6 (V-)
/CV INPUT 1: J4.T, R6.1
/CV INPUT 2: J5.T, R18.1
/INPUT: J2.T, R2.1
/OUTPUT: J3.T, R4.2
GND: C1.2, C2.1, C3.2, C4.2, C5.1, C6.1, C7.2, C8.1, C10.2, D4.1 (K), J1.3 (gnd), J1.4 (gnd), J1.5 (gnd), J1.6 (gnd), J1.7 (gnd), J1.8 (gnd), J2.S, J3.S, J4.S, J5.S, Q2.2 (E), R3.2, R14.2, R15.2, U1.3 (+), U1.10 (+), U1.12 (+), U2.13 (-)
unnamed: D1.2 (A), J1.9 (+12V), J1.10 (+12V)
unnamed: D2.1 (K), J1.1 (-12V), J1.2 (-12V)
unnamed: C9.2, D3.2 (A), R1.2, R4.1, U1.1
unnamed: C10.1, D3.1 (K), R14.1, U1.6 (-)
unnamed: D4.2 (A), R17.1
unnamed: Q1.1 (B), R5.2, R10.1, U1.14
unnamed: Q1.2 (E), Q2.1 (B), R13.2
unnamed: Q2.3 (C), SW1.1 (A)
unnamed: R2.2, RV1.3
unnamed: R3.1, RV1.1
unnamed: R7.1, RV2.2
unnamed: R8.1, RV2.3
unnamed: R9.2, RV2.1
unnamed: R12.2, U2.16
unnamed: R17.2, U1.7
unnamed: R19.1, RV3.1
unnamed: R20.2, RV3.3
unnamed: R12.1, SW1.2 (B)
unnamed: R11.2, SW1.3 (C), U1.8
unnamed: C9.1, R1.1, U1.2 (-), U2.12
unnamed: R15.1, R16.2, U1.5 (+)
unnamed: R10.2, R11.1, U1.9 (-)
unnamed: R5.1, R6.2, R7.2, R18.2, RV3.2, U1.13 (-)
unnamed: RV1.2, U2.14 (+)

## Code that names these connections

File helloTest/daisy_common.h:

#include "daisy_seed.h"
using namespace daisy::seed;
using namespace daisy;


namespace daisy
{

class daisyCommon
{
    public:
    daisyCommon() {}
    ~daisyCommon() {}

    enum jacks
    {
	    in_1 = 0, in_2, in_3, gate_1_in_4, in_5, in_6, in_7, gate_2_in_8
    };
    enum mux
    {
        mux_x = 0, mux_y
    };
    enum mux_x_channel
    {
        knob_1_chan = 0, knob_3_chan, knob_5_chan, knob_4_chan
    };
    enum mux_y_channel
    {
        knob_2_chan = 0, knob_8_chan, knob_6_chan, knob_7_chan
    };
    enum knobs
    {
        knob_1 = 0, knob_2, knob_3, knob_4, knob_5, knob_6, knob_7, knob_8
    };
    enum jack_gpio_direction
    {
        input = 0, output
    };
    enum jack_config
    {
        audio_enable = 0, dac_enable, gate_enable, gpio_enable, adc_enable, disable
    };

    struct input_configs
    {

    }cv_config;

    GPIO OUT_1_AUDIO_EN;
	GPIO OUT_2_AUDIO_EN;
	GPIO OUT_1_DAC_EN;
	GPIO OUT_2_DAC_EN;
    GPIO GATE_1_EN;
	GPIO GATE_2_EN;
	GPIO IN_4_EN;
	GPIO IN_8_EN;

    GPIO IN_1;
    GPIO IN_2;
    GPIO IN_3;
    GPIO GATE_1_IN_4;
    GPIO IN_5;
    GPIO IN_6;
    GPIO IN_7;
    GPIO GATE_2_IN_8;

    Switch3 toggle_left;
    Switch3 toggle_right;
    Switch button;
    knobs knob;

    void Init(bool boost = false);
    void add_knob(int user_name, int knob_num);
    float get_knob(int user_name);
    void print_knob();
    void add_cv(int user_name, int jack_num);
    float get_cv(int user_name);
    void add_dual_control(int user_name, int jack_num, int knob_num);
    float get_dual_control(int user_name);

    //void add_dac(int user_name, int jack);
    DaisySeed seed;

    private:
    void InitGPIO_MUX();
    void InitToggle();
    void InitADC();
    void InitButton();
    Pin getCVPin(int jack);
    Pin getGPIOPin(int jack);
    GPIO getGPIO(int jack);
    int knob_1_user_name = -1, 
        knob_2_user_name = -1,
        knob_3_user_name = -1, 
        knob_4_user_name = -1, 
        knob_5_user_name = -1, 
        knob_6_user_name = -1, 
        knob_7_user_name = -1, 
        knob_8_user_name = -1;
    int jack_1_user_name = -1,
        jack_2_user_name = -1,
        jack_3_user_name = -1,
        jack_4_user_name = -1,
        jack_5_user_name = -1,
        jack_6_user_name = -1,
        jack_7_user_name = -1,
        jack_8_user_name = -1;
    int out_1_mode = audio_enable;
    int out_2_mode = audio_enable;
    int gate_1_in_4_mode = disable;
    int gate_2_in_8_mode = disable;
    int in_1_mode = disable;
    int in_2_mode = disable;
    int in_3_mode = disable;
    int in_5_mode = disable;
    int in_6_mode = disable;
    int in_7_mode = disable;
    int in_1_adc_chan = -1,
        in_2_adc_chan = -1,
        in_3_adc_chan = -1,
        in_4_adc_chan = -1,
        in_5_adc_chan = -1,
        in_6_adc_chan = -1,
        in_7_adc_chan = -1,
        in_8_adc_chan = -1;

    int get_mux(int knob_user_name);
    int get_knob_adc_chan(int knob_user_name);
    int get_cv_adc_chan(int adc_user_name);
    int adc_channel_count = 2;

};
}

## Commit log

2023-04-12 added seed interface circuits
2023-04-17 Updated CV circuit for totally off knob
2023-04-17 added lm13700 sub to repo
2023-04-17 drum osc first commit
2023-04-18 Adjusted CV gains
2023-04-20 Improved CV circuit for linear and exp
2023-04-21 modified .gitignore
2023-04-22 fixed .gitignore
2023-04-24 finalized schematic started layout
2023-05-21 drum osc updates
2023-06-15 troubleshooting improving waveshaper
2023-12-16 Updated Seed Interface
2023-12-22 added attenuverter and dc
2024-01-14 Rev 0 for common platform
2024-01-29 working hardware demo
2024-03-03 knob functionality added to board support
2024-03-09 added cv and dual cv/knob control
2024-06-02 added board support and FHO project
2024-06-02 reorganize folder structure
2024-06-03 reorganize and add comments
2024-06-03 reorganize and comment
2024-06-03 uncomment readme
2024-06-05 documentation update
2024-06-19 working VCA EG module
2024-06-20 added mixing, leds, and button
2024-06-21 added readme
2024-07-02 added ECO comments
2024-07-02 basic kick implementation
2024-07-02 rebuild
2024-08-03 initial progress percussion
2024-08-07 attentuverter schematic complete
2024-08-14 attenuverter complete
2024-08-17 created fabrication output
2024-08-17 added golden faceplate
2024-08-17 reorganize folders
2024-09-19 rev A0 output module
2024-09-26 proto order
2025-01-10 frequency curves added, wip on morph
2025-01-10 update output module production mistakes
2025-01-12 fix rev A errors
2025-03-09 200 Plattform Pending Design Review
2025-03-17 board design review complete
2025-03-29 finished top level drawing
2025-03-30 Final Design Review 200 Series
2025-07-13 misc WIP
2025-09-17 filter module complete
2025-09-21 basic VCAENV WIP for first rack
2025-11-18 Base Rack and FHO WIP
2026-03-22 oscillator simulation and hihat simulation wip
2026-03-25 added E12 resistors
2026-03-26 wip on 401 oscillator. Core started
2026-04-21 401 oscillator wip
2026-05-02 wip on hihat digital module
2026-05-17 first pass of 401 VCO schematic
2026-06-10 404 VCA first pass layout/schematic
2026-06-17 403 filter wip
2026-06-21 fist pass 403VCF wip
